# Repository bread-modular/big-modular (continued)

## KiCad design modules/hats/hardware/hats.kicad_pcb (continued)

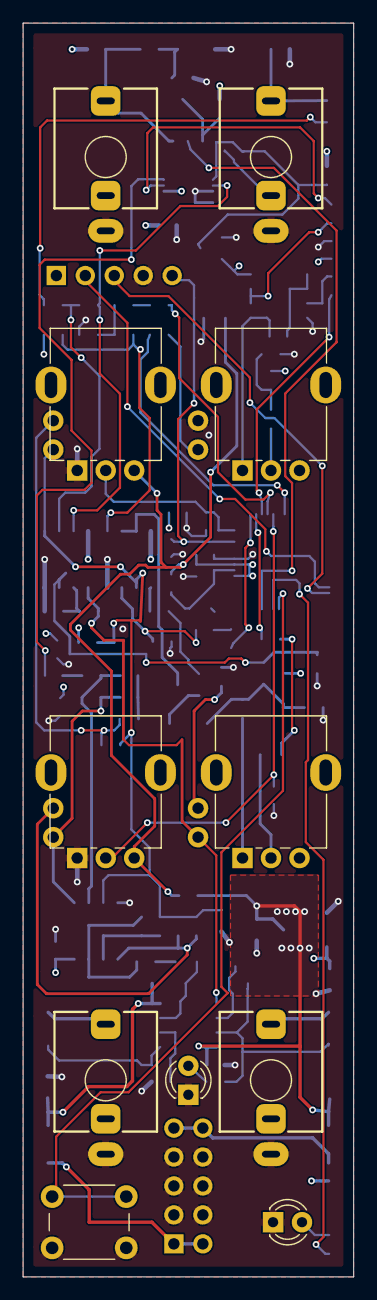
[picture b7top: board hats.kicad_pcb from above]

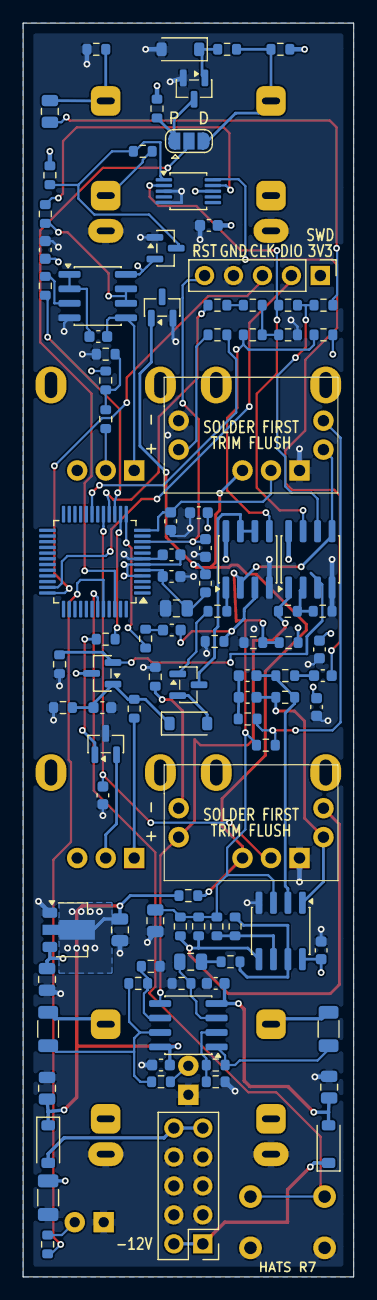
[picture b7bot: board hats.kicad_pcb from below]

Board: 4 copper layers, 29.0 x 110.0 mm, 113 parts (102 on the bottom side), 75 nets.

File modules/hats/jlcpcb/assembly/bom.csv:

Comment,Designator,Footprint,LCSC Part #,Quantity,Manufacturer,MPN
10u,"C1, C2, C4",C_0805_2012Metric,C15850,3,Samsung,CL21A106KAYNNNE
1u,"C3, C10, C21, C24",C_0805_2012Metric,C28323,4,Samsung,CL21B105KBFNNNE
100u,C5,C_1206_3216Metric,C15008,1,Samsung,CL31A107MQHNNNE
100n,"C6, C9, C11, C16, C19, C20, C22, C23, C25, C26",C_0603_1608Metric,C14663,10,YAGEO,CC0603KRX7R9BB104
4.7u,"C7, C18",C_0603_1608Metric,C19666,2,Samsung,CL10A475KO8NNNC
100p,"C8, C12",C_0603_1608Metric,C14858,2,Samsung,CL10C101JB8NNNC
1n,"C13, C14",C_0603_1608Metric,C1588,2,Samsung,CL10B102KB8NNNC
47u,C15,C_0805_2012Metric,C16780,1,Samsung,CL21A476MQYNNNE
10n,"C17, C27, C28",C_0603_1608Metric,C57112,3,FH (Guangdong Fenghua),0603B103K500NT
B5819W,"D1, D2, D4",D_SOD-123,C8598,3,CJ (Jiangsu Changjing),B5819W SL
1N4148W,D3,D_SOD-123,C81598,1,ST(Semtech),1N4148W
BAV199,D7,SOT-23,C40919,1,Nexperia,"BAV199,215"
600R@100MHz,FB1,L_0603_1608Metric,C1002,1,Sunlord,GZ1608D601TF
MMBT3904,Q1,SOT-23,C20526,1,CJ (Jiangsu Changjing),MMBT3904(RANGE:100-300)
SS8050,"Q2, Q4",SOT-23,C431710,2,MDD(Microdiode Semiconductor),SS8050
SS8550,Q3,SOT-23,C364314,1,MDD(Microdiode Semiconductor),SS8550
100k,"R1, R11, R12, R15, R27, R30, R31, R38, R39, R40, R45",R_0603_1608Metric,C25803,11,UNI-ROYAL,0603WAF1003T5E
10k,"R2, R21, R26, R29, R37, R42",R_0603_1608Metric,C25804,6,UNI-ROYAL,0603WAF1002T5E
22k,"R3, R20, R34, R49",R_0603_1608Metric,C31850,4,UNI-ROYAL,0603WAF2202T5E
1k,"R6, R8, R9, R10, R17, R22, R24, R25, R47, R48",R_0603_1608Metric,C21190,10,UNI-ROYAL,0603WAF1001T5E
330,"R7, R18, R19, R23, R28, R35, R51",R_0603_1608Metric,C23138,7,UNI-ROYAL,0603WAF3300T5E
33k,R13,R_0603_1608Metric,C4216,1,UNI-ROYAL,0603WAF3302T5E
470k,R14,R_0603_1608Metric,C23178,1,UNI-ROYAL,0603WAF4703T5E
200k,"R16, R36",R_0603_1608Metric,C25811,2,UNI-ROYAL,0603WAF2003T5E
1M,"R32, R33",R_0603_1608Metric,C22935,2,UNI-ROYAL,0603WAF1004T5E
20k,R41,R_0603_1608Metric,C4184,1,UNI-ROYAL,0603WAF2002T5E
1k,"R43, R46",R_1206_3216Metric,C2074262,2,ROHM,ESR18EZPF1001
51k,"R44, R50",R_0603_1608Metric,C23196,2,UNI-ROYAL,0603WAF5102T5E
HT7533-1,U1,SOT-89-3,C14289,1,Holtek,HT7533-1
STM32G071C8T6,U2,LQFP-48_7x7mm_P0.5mm,C529341,1,STMicroelectronics,STM32G071C8T6
MCP6002,"U4, U6, U8, U9",SOIC-8_3.9x4.9mm_P1.27mm,C7377,4,Microchip,MCP6002T-I/SN
TS5A23157,U5,TSSOP-10_3x3mm_P0.5mm,C11133,1,Texas Instruments,TS5A23157DGSR
TL072,U10,SOIC-8_3.9x4.9mm_P1.27mm,C6961,1,STMicroelectronics,TL072CDT

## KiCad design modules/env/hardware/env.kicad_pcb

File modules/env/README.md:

# ENV: MIDI envelope (6HP)

The ACID envelope on its own module: Bread Modular **ENV** on one ATtiny1616 at 5 V (the same HT7550-1 supply as our 8bit),
triggered by MIDI notes, with three envelope models, knob recording and a protected 0..5 V
output.

| Panel (top to bottom) | Circuit |
|---|---|
| **GATE IN**, **MIDI IN** (top row) | GATE: NPN buffer (~1.9 V threshold, ±12 V safe) + jack detect: a patched GATE IN bypasses MIDI notes. MIDI: 8bit / ACID NPN front end, JP1 protected/direct jumper |
| **ATTACK**, **RELEASE** | BM ENV time knobs, 50k dividers (attack = hold in HR mode), 30 mm apart |
| **MODE** button + **HR / AR / ASR** LEDs (one row) | Envelope model select (BM ENV algorithms); the selected LED stays lit |
| **REC** button + LED | Records the knob positions (4-bar loop on MIDI clock) |
| **ENV OUT**, **ENV** LED, **MIDI OUT** (bottom row) | Scaled DAC ~0..3.3 V (INT43V, codes 0..194) -> TL072 x1.51 -> 0..5 V, 1k 0.5 W series; the LED shows the envelope level (driven by the output amp). MIDI OUT is a passive thru wired to MIDI IN (daisy chain) |

**Status: S5 schematic (ERC 0, every net wired; adds R20 470k from ENV OUT to -12 V so a silent envelope idles at about -25 mV) + P7 THT placement + R2 manual routing (R1 + R20) (2 layers,
DRC 0, unconnected 0, parity 0; B silk JP1 / UPDI labels); 6HP panel. JLCPCB export in
[`jlcpcb/`](jlcpcb/README.md) (S5/R2, 2026-11-18, bottom Economic, 37 parts / 19 rows), not supplier-accepted, not built.
Firmware in [`firmware/`](firmware/README.md) (JP1 p/d builds), compiled, not bench-tested.** R5-R8 (HR/AR/ASR/REC indicators) are now 1k; R13 (ENV LED) was already 1k.

**Firmware contract:** 4.34 V DAC setting at a 5 V supply, scale the envelope to DAC codes
0..194; use VDD for the knob ADC reference. Use JP1 **P/protected** for 3.3 V MIDI senders
(direct mode is 5 V logic only) and a 5 V-compatible UPDI programmer.

```sh
python3 -B tools/import_footprints.py   # one-time library import (pcbnew)
python3 -B tools/build_schematic.py     # schematic (placement by hand, wires by its router)
python3 -B tools/build_layout.py        # P7: THT placement + parked SMD. Do NOT rerun: the board is routed
(cd ../.. && python3 -B opt/kicad-tools/kicad_tools.py check --config modules/env/tools/kicad-project.json \
   --reports modules/env/research/check-NEW)
```

Read [`Code.md`](Code.md) before changing hardware.

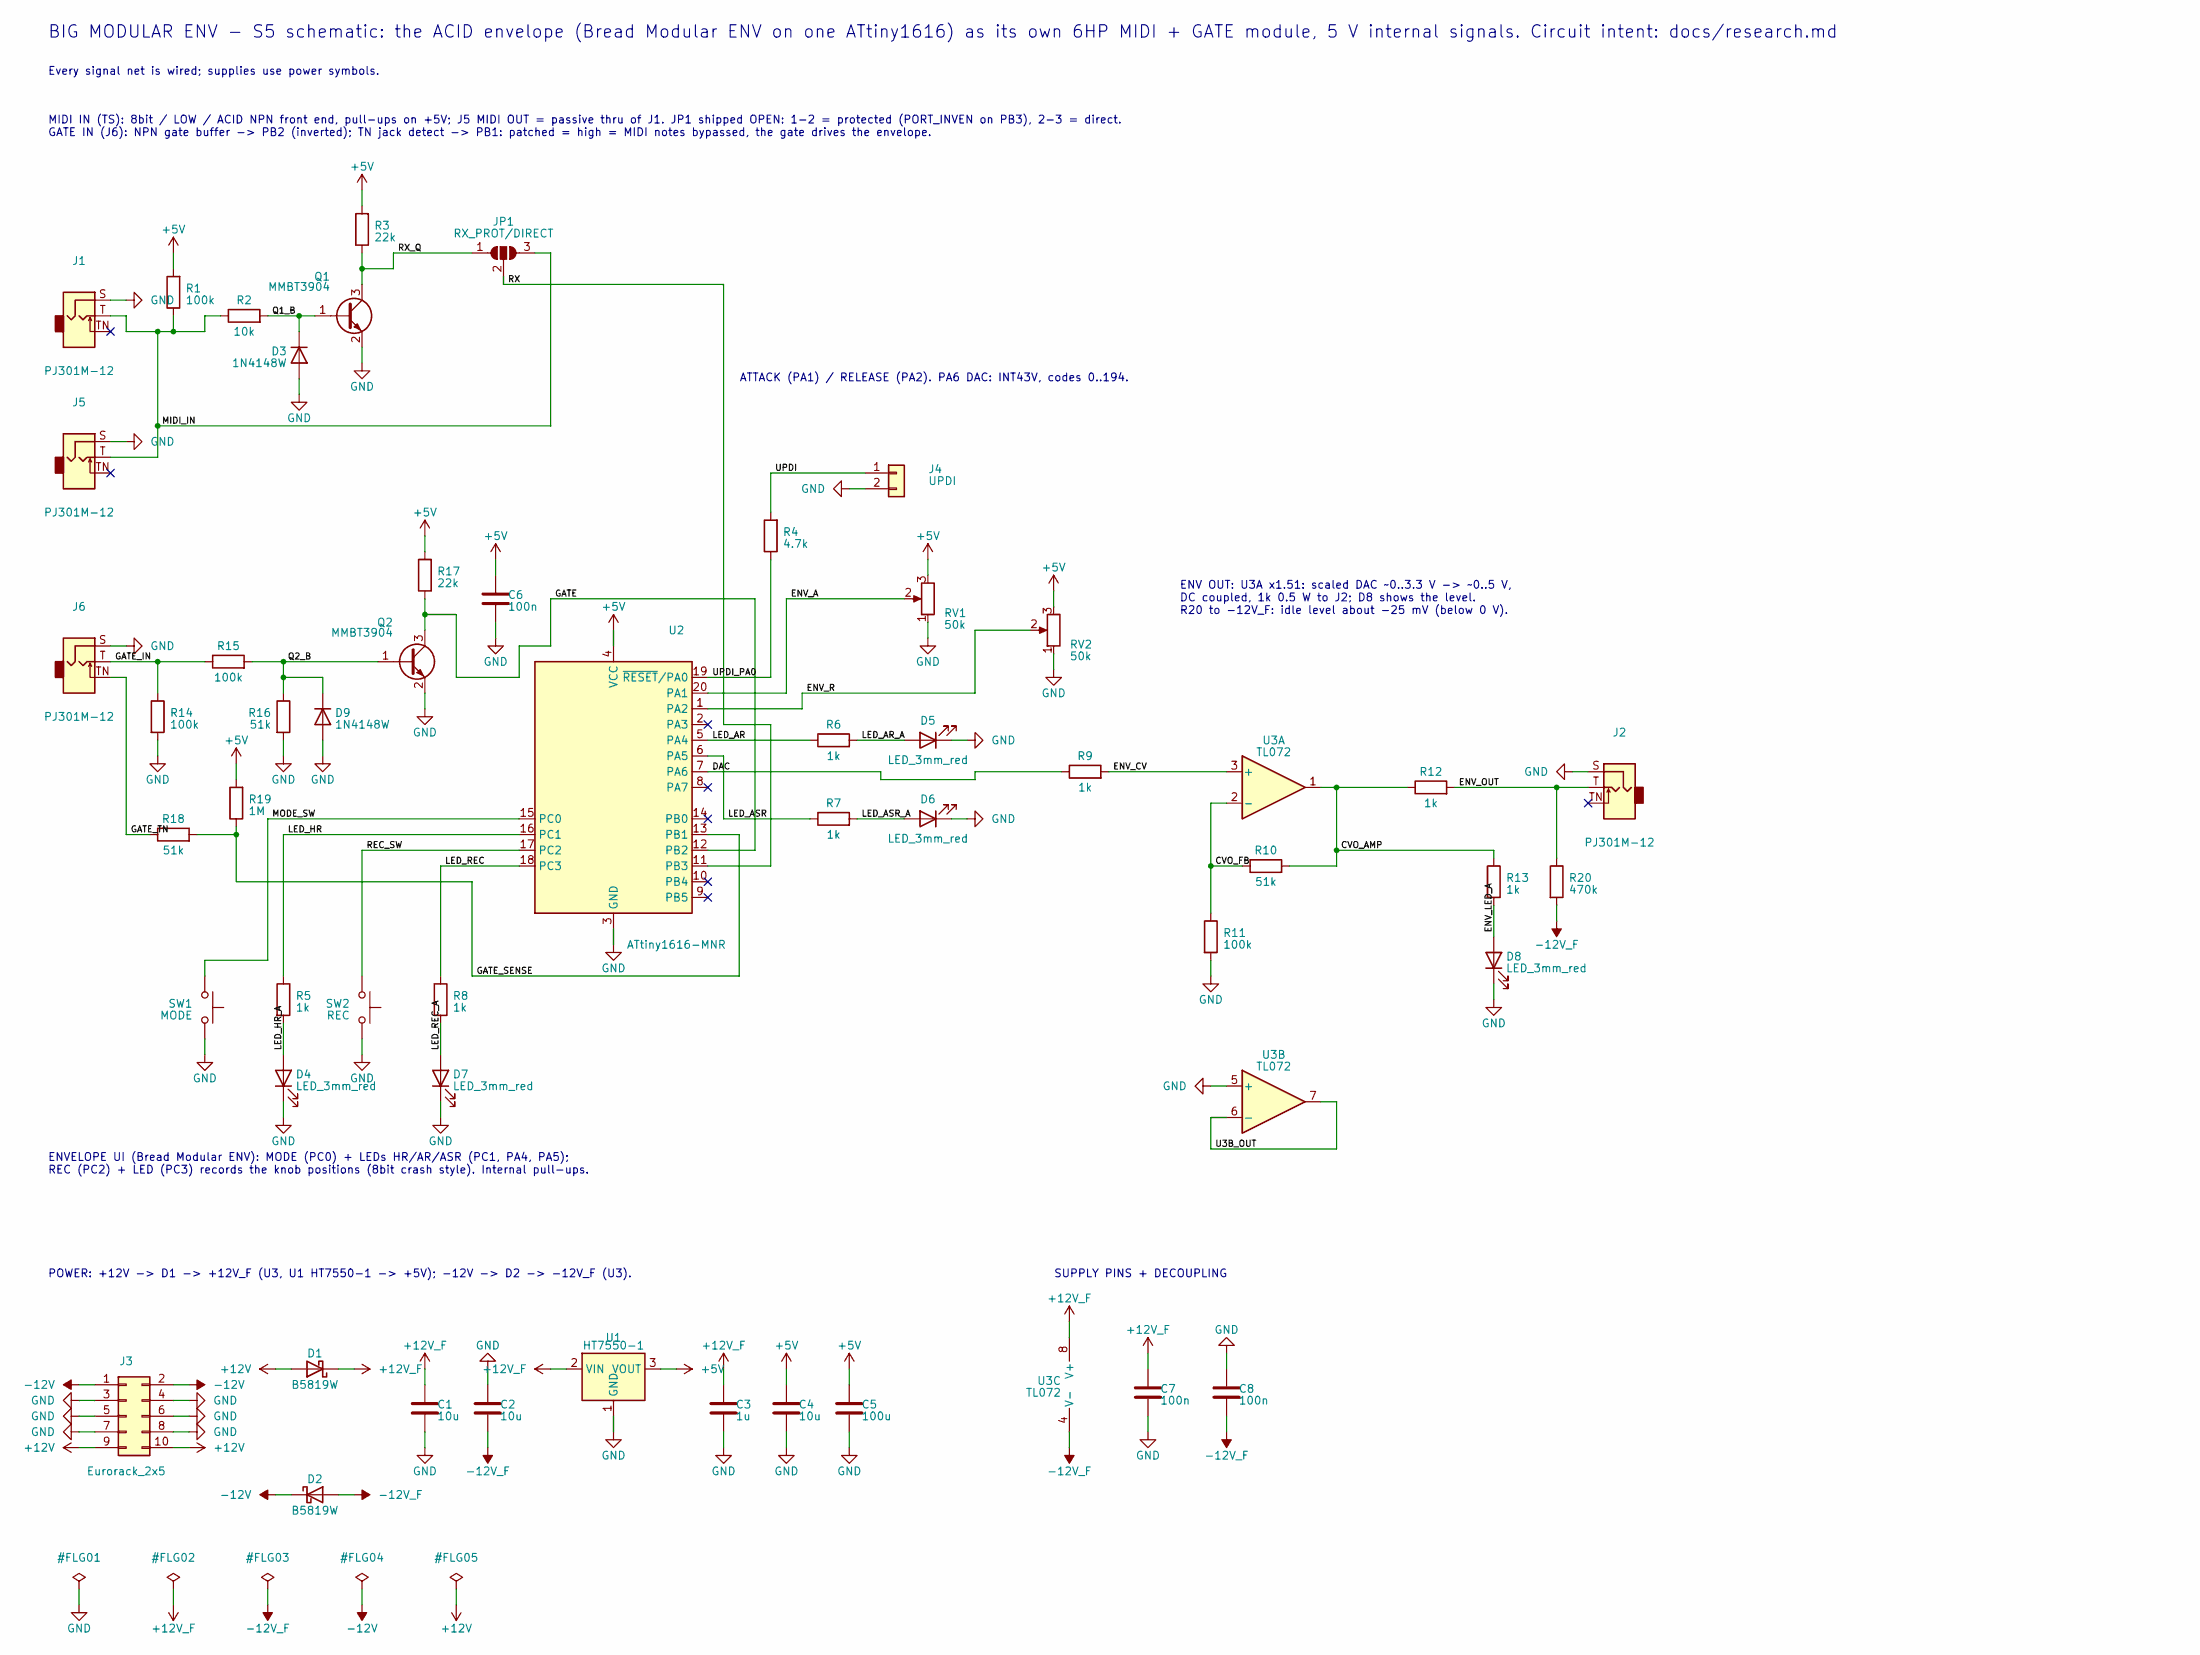
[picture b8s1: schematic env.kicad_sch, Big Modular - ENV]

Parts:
C1, C2, C4: 10u; C_0805_2012Metric; Voltage 25V; MPN CL21A106KAYNNNE; LCSC C15850
C3: 1u; C_0805_2012Metric; Voltage 50V; MPN CL21B105KBFNNNE; LCSC C28323
C5: 100u; C_1206_3216Metric; Voltage 6.3V; MPN CL31A107MQHNNNE; LCSC C15008
C6, C7, C8: 100n; C_0603_1608Metric; Voltage 50V; MPN CC0603KRX7R9BB104; LCSC C14663
D1, D2: B5819W; D_SOD-123; MPN B5819W SL; LCSC C8598
D3, D9: 1N4148W; D_SOD-123; MPN 1N4148W; LCSC C81598
D4, D5, D6, D7, D8: LED_3mm_red; LED_D3.0mm
J1, J2, J5, J6: PJ301M-12; Jack_3.5mm_QingPu_WQP-PJ301M-12_Vertical
J3: Eurorack_2x5; PinHeader_2x05_P2.54mm_Vertical
J4: UPDI; PinHeader_1x02_P2.54mm_Vertical
JP1: RX_PROT/DIRECT; SolderJumper-3_P1.3mm_Open_RoundedPad1.0x1.5mm
Q1, Q2: MMBT3904; SOT-23; MPN MMBT3904(RANGE:100-300); LCSC C20526
R1, R11, R14, R15: 100k; R_0603_1608Metric; MPN 0603WAF1003T5E; LCSC C25803
R2: 10k; R_0603_1608Metric; MPN 0603WAF1002T5E; LCSC C25804
R3, R17: 22k; R_0603_1608Metric; MPN 0603WAF2202T5E; LCSC C31850
R4: 4.7k; R_0603_1608Metric; MPN 0603WAF4701T5E; LCSC C23162
R5, R6, R7, R8, R9, R13: 1k; R_0603_1608Metric; MPN 0603WAF1001T5E; LCSC C21190
R10, R16, R18: 51k; R_0603_1608Metric; MPN 0603WAF5102T5E; LCSC C23196
R12: 1k; R_1206_3216Metric; MPN ESR18EZPF1001; LCSC C2074262
R19: 1M; R_0603_1608Metric; MPN 0603WAF1004T5E; LCSC C22935
R20: 470k; R_0603_1608Metric; MPN 0603WAF4703T5E; LCSC C23178
RV1, RV2: 50k; Potentiometer_RV09
SW1: MODE; SW_PUSH_6mm_H7.3mm; MPN 6x6x7 mm THT tact switch, 4 pins (gener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
SW2: REC; SW_PUSH_6mm_H7.3mm; MPN 6x6x7 mm THT tact switch, 4 pins (gener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
U1: HT7550-1; SOT-89-3; MPN HT7550-1; LCSC C16106
U2: ATtiny1616-MNR; VQFN-20-1EP_3x3mm_P0.4mm_EP1.7x1.7mm; MPN ATTINY1616-MNR; LCSC C507118
U3: TL072; SOIC-8_3.9x4.9mm_P1.27mm; MPN TL072CDT; LCSC C6961

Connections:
+5V: C4.1, C5.1, C6.1, R1.2, R3.2, R17.2, R19.2, RV1.3, RV2.3, U1.3 (VOUT), U2.4 (VCC)
+12V: D1.2 (A), J3.9, J3.10
+12V_F: C1.1, C3.1, C7.1, D1.1 (K), U1.2 (VIN), U3.8 (V+)
-12V: D2.1 (K), J3.1, J3.2
-12V_F: C2.2, C8.2, D2.2 (A), R20.2, U3.4 (V-)
/CVO_AMP: R10.2, R12.1, R13.1, U3.1
/CVO_FB: R10.1, R11.1, U3.2 (-)
/DAC: R9.1, U2.7 (PA6)
/ENV_A: RV1.2, U2.20 (PA1)
/ENV_CV: R9.2, U3.3 (+)
/ENV_LED_A: D8.2 (A), R13.2
/ENV_OUT: J2.T, R12.2, R20.1
/ENV_R: RV2.2, U2.1 (PA2)
/GATE: Q2.3 (C), R17.1, U2.12 (PB2)
/GATE_IN: J6.T, R14.1, R15.1
/GATE_SENSE: R18.2, R19.1, U2.13 (PB1)
/GATE_TN: J6.TN, R18.1
/LED_AR: R6.1, U2.5 (PA4)
/LED_AR_A: D5.2 (A), R6.2
/LED_ASR: R7.1, U2.6 (PA5)
/LED_ASR_A: D6.2 (A), R7.2
/LED_HR: R5.1, U2.16 (PC1)
/LED_HR_A: D4.2 (A), R5.2
/LED_REC: R8.1, U2.18 (PC3)
/LED_REC_A: D7.2 (A), R8.2
/MIDI_IN: J1.T, J5.T, JP1.3 (B), R1.1, R2.1
/MODE_SW: SW1.1, U2.15 (PC0)
/Q1_B: D3.1 (K), Q1.1 (B), R2.2
/Q2_B: D9.1 (K), Q2.1 (B), R15.2, R16.1
/REC_SW: SW2.1, U2.17 (PC2)
/RX: JP1.2 (C), U2.11 (PB3)
/RX_Q: JP1.1 (A), Q1.3 (C), R3.1
/U3B_OUT: U3.6 (-), U3.7
/UPDI: J4.1, R4.2
/UPDI_PA0: R4.1, U2.19 (~RESET/PA0)
GND: C1.2, C2.1, C3.2, C4.2, C5.2, C6.2, C7.2, C8.1, D3.2 (A), D4.1 (K), D5.1 (K), D6.1 (K), D7.1 (K), D8.1 (K), D9.2 (A), J1.S, J2.S, J3.3, J3.4, J3.5, J3.6, J3.7, J3.8, J4.2, J5.S, J6.S, Q1.2 (E), Q2.2 (E), R11.2, R14.2, R16.2, RV1.1, RV2.1, SW1.2, SW2.2, U1.1 (GND), U2.3 (GND), U2.21 (GND), U3.5 (+)

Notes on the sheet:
ATTACK (PA1) / RELEASE (PA2). PA6 DAC: INT43V, codes 0..194.
Every signal net is wired; supplies use power symbols.
ENV OUT: U3A x1.51: scaled DAC ~0..3.3 V -> ~0..5 V, DC coupled, 1k 0.5 W to J2; D8 shows the level. R20 to -12V_F: idle level about -25 mV (below 0 V).
ENVELOPE UI (Bread Modular ENV): MODE (PC0) + LEDs HR/AR/ASR (PC1, PA4, PA5); REC (PC2) + LED (PC3) records the knob positions (8bit crash style). Internal pull-ups.
MIDI IN (TS): 8bit / LOW / ACID NPN front end, pull-ups on +5V; J5 MIDI OUT = passive thru of J1. JP1 shipped OPEN: 1-2 = protected (PORT_INVEN on PB3), 2-3 = direct. GATE IN (J6): NPN gate buffer -> PB2 (inverted); TN jack detect -> PB1: patched = high = MIDI notes bypassed, the gate drives the en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
BIG MODULAR ENV - S5 schematic: the ACID envelope (Bread Modular ENV on one ATtiny1616) as its own 6HP MIDI + GATE module, 5 V internal signals. Circuit intent: docs/research.md
SUPPLY PINS + DECOUPLING
POWER: +12V -> D1 -> +12V_F (U3, U1 HT7550-1 -> +5V); -12V -> D2 -> -12V_F (U3).

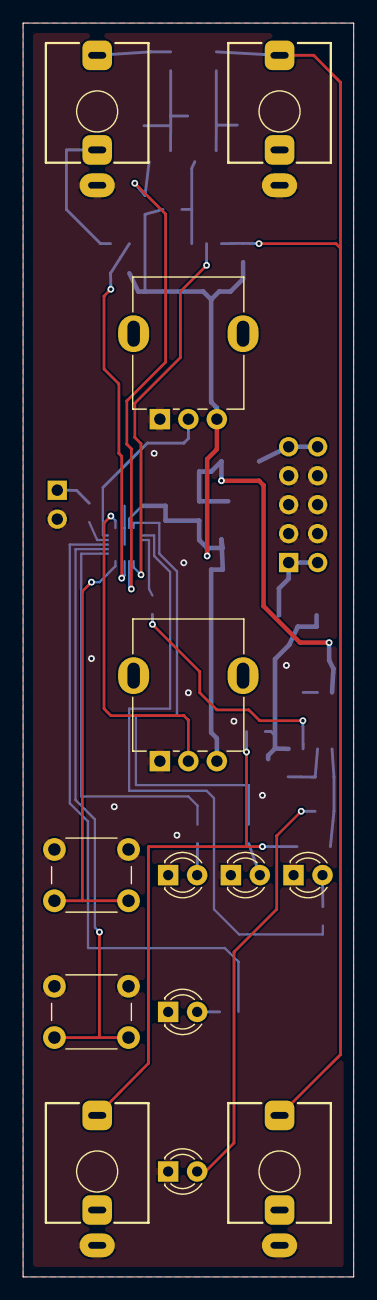
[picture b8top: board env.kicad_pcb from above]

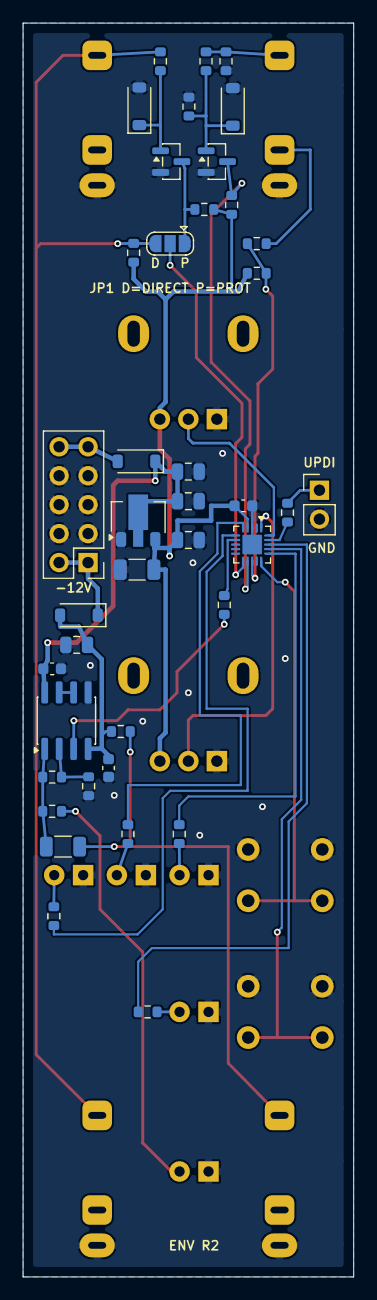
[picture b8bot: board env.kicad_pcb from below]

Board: 2 copper layers, 29.0 x 110.0 mm, 53 parts (40 on the bottom side), 36 nets.

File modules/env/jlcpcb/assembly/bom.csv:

Comment,Designator,Footprint,LCSC Part #,Quantity,Manufacturer,MPN
10u,"C1, C2, C4",C_0805_2012Metric,C15850,3,Samsung,CL21A106KAYNNNE
1u,C3,C_0805_2012Metric,C28323,1,Samsung,CL21B105KBFNNNE
100u,C5,C_1206_3216Metric,C15008,1,Samsung,CL31A107MQHNNNE
100n,"C6, C7, C8",C_0603_1608Metric,C14663,3,YAGEO,CC0603KRX7R9BB104
B5819W,"D1, D2",D_SOD-123,C8598,2,CJ (Jiangsu Changjing),B5819W SL
1N4148W,"D3, D9",D_SOD-123,C81598,2,ST(Semtech),1N4148W
MMBT3904,"Q1, Q2",SOT-23,C20526,2,CJ (Jiangsu Changjing),MMBT3904(RANGE:100-300)
100k,"R1, R11, R14, R15",R_0603_1608Metric,C25803,4,UNI-ROYAL,0603WAF1003T5E
10k,R2,R_0603_1608Metric,C25804,1,UNI-ROYAL,0603WAF1002T5E
22k,"R3, R17",R_0603_1608Metric,C31850,2,UNI-ROYAL,0603WAF2202T5E
4.7k,R4,R_0603_1608Metric,C23162,1,UNI-ROYAL,0603WAF4701T5E
1k,"R5, R6, R7, R8, R9, R13",R_0603_1608Metric,C21190,6,UNI-ROYAL,0603WAF1001T5E
51k,"R10, R16, R18",R_0603_1608Metric,C23196,3,UNI-ROYAL,0603WAF5102T5E
1k,R12,R_1206_3216Metric,C2074262,1,ROHM,ESR18EZPF1001
1M,R19,R_0603_1608Metric,C22935,1,UNI-ROYAL,0603WAF1004T5E
470k,R20,R_0603_1608Metric,C23178,1,UNI-ROYAL,0603WAF4703T5E
HT7550-1,U1,SOT-89-3,C16106,1,Holtek,HT7550-1
ATtiny1616-MNR,U2,VQFN-20-1EP_3x3mm_P0.4mm_EP1.7x1.7mm,C507118,1,Microchip,ATTINY1616-MNR
TL072,U3,SOIC-8_3.9x4.9mm_P1.27mm,C6961,1,STMicroelectronics,TL072CDT

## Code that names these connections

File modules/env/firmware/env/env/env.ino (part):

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// GATE IN:
//
//   * Gate: MIDI note on/off (channel 1), or GATE IN when a cable is patched
//     (PB1 jack detect high): then MIDI notes are bypassed and the jack gate
//     (PB2, inverted by Q2) drives the envelope.
//   * Envelope (BM ENV 1.2.1) on the DAC (PA6 -> TL072 x1.51 -> ENV OUT
//     0..5 V). ATTACK (PA1, hold in HR) and RELEASE (PA2) set the times, plus
//     MIDI CC22 / CC75 as BM. MODE (PC0, a click) cycles HR / AR / ASR, stored
//     in EEPROM; the selected model's LED (PC1 / PA4 / PA5) stays lit at
//     10 % (the ENV LED at the jack shows the envelope level).
//   * REC (PC2 / LED PC3): 4-bar ATTACK/RELEASE motion recorder on MIDI clock
//     (shared lib/CvRecorder, as ACID): click to record (LED blinks), after
//     4 bars it loops (LED solid), hold REC + turn a knob to overdub it,
//     click again for the live knobs.
//
// The USART runs receive-only: its TX pin PB2 is GATE IN on this board.
// ----------------------------------------------------------------------------

// JP1 on the ENV carrier picks the MIDI input path (set by ../../jumper.sh):
//   P (protected) = NPN front end (Q1), which inverts the UART data -> 1
//   D (direct)    = jack tip straight to PB3, 5 V logic senders only -> 0
#ifndef MIDI_RX_INVERT
#error "MIDI_RX_INVERT must be set: build with ../../compile.sh p|d"
#endif

#define PIN_CV1          PIN_PA1   // ATTACK knob (hold time in HR)
#define PIN_CV2          PIN_PA2   // RELEASE knob
#define MODE_BUTTON_PIN  PIN_PC0   // envelope model (BM ENV algo button)
#define LED_HR           PIN_PC1
#define LED_AR           PIN_PA4
#define LED_ASR          PIN_PA5
#define REC_BUTTON_PIN   PIN_PC2
#define REC_LED_PIN      PIN_PC3
#define GATE_IN_PIN      PIN_PB2   // Q2 collector: LOW = gate high at the jack
#define GATE_SENSE_PIN   PIN_PB1   // HIGH = GATE IN patched (TN open)

#define ALGO_HOLD_RELEASE 0
#define ALGO_ATTACK_RELEASE 1
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#define GATE_SENSE_MS 20           // jack detect must hold this long to switch

// MODE LED brightness: TCA0 in split mode (TCD0 is millis), 20 MHz / 256 /
// 256 = 305 Hz, duty = count / 256. PA4 (WO4, HCMP1) and PA5 (WO5, HCMP2)
// are hardware PWM. PC1 has no TCA output, so the low counter switches it in
// software (LCMP0 on, LUNF off); those two interrupts run only while the HR
// LED is lit.
#define LED_PERCENT 10             // brightness of the selected MODE LED
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EnvelopeGenerator *envelope;

ToggleMode algoMode(MODE_BUTTON_PIN, 1, 3);        // EEPROM index 1, as BM
CvRecorder recorder(REC_BUTTON_PIN, REC_LED_PIN);

const uint8_t modeLeds[3] = {LED_HR, LED_AR, LED_ASR};

uint16_t liveCV1 = 0;              // ATTACK / RELEASE knobs (recorder input)
uint16_t liveCV2 = 0;
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int modCV2 = 0;                    // MIDI CC75 (release time)

bool midiGate = false;
byte gateNote = 0;                 // note that holds the gate
bool gatePatched = false;          // debounced PB1 jack detect
byte selectedLed = 0;              // index into modeLeds

void handleAlgoModeChange(byte newMode) {
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  TCA0.SPLIT.CTRLA = TCA_SPLIT_CLKSEL_DIV256_gc | TCA_SPLIT_ENABLE_bm;
}

// PC1 (HR) software PWM: the down-counting low counter matches LCMP0 =
// duty - 1, so PC1 is high for duty counts until the underflow.
ISR(TCA0_LCMP0_vect) {
  PORTC.OUTSET = PIN1_bm;
  TCA0.SPLIT.INTFLAGS = TCA_SPLIT_LCMP0_bm;
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
  uint8_t outputs = 0;
  if (duty && led == 1) {
    outputs = TCA_SPLIT_HCMP1EN_bm;    // PA4 (AR)
  } else if (duty && led == 2) {
    outputs = TCA_SPLIT_HCMP2EN_bm;    // PA5 (ASR)
  }
  TCA0.SPLIT.CTRLB = outputs;

  const bool soft = duty && led == 0;  // PC1 (HR)
  TCA0.SPLIT.INTCTRL = soft ? TCA_SPLIT_LUNF_bm | TCA_SPLIT_LCMP0_bm : 0;
  if (!soft) {
    PORTC.OUTCLR = PIN1_bm;
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}

void handleNoteOff(byte channel, byte note, byte velocity) {
  // Only the latest note closes the gate: an overlapping (legato) note keeps
  // the envelope open instead of releasing it under the held note.
  if (note == gateNote) {
    midiGate = false;
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  liveCV2 = analogRead(PIN_CV2);
}

// PB1 jack detect, debounced: the TN contact opens / closes while a plug
// slides in, so the new state must hold GATE_SENSE_MS before it switches.
void updateGateSense() {
  static bool lastRaw = false;
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// Envelope gate: GATE IN when patched (MIDI notes bypassed), else MIDI.
bool currentGate() {
  if (gatePatched) {
    return !(VPORTB.IN & PIN2_bm);     // Q2 inverts: PB2 low = gate high
  }
  return midiGate;
}
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
void setup() {
  // Unused pins (no-connect on the carrier): pulled up, not floating.
  pinMode(PIN_PA3, INPUT_PULLUP);
  pinMode(PIN_PA7, INPUT_PULLUP);
  pinMode(PIN_PB0, INPUT_PULLUP);
  pinMode(PIN_PB4, INPUT_PULLUP);
  pinMode(PIN_PB5, INPUT_PULLUP);

  // GATE IN: R17 22k pull-up and R19 1M jack-detect pull-up on the board.
  pinMode(GATE_IN_PIN, INPUT);
  pinMode(GATE_SENSE_PIN, INPUT);
  gatePatched = VPORTB.IN & PIN1_bm;

  // MIDI, receive only (serialMIDI.h): listen to channel 1 only.
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  MIDI.turnThruOff();
#if MIDI_RX_INVERT
  // JP1 = P: the NPN input stage inverts the MIDI UART data, so invert
  // PB3 (RX) in the port before the USART samples it.
  PORTB.PIN3CTRL |= PORT_INVEN_bm;
#endif
  MIDI.setHandleNoteOn(handleNoteOn);
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  (void)analogRead(PIN_CV1);       // throwaway warm-up read
  readKnobs();

  // DAC0 on PA6 with the internal 4.34 V reference (needs VDD >= 4.75 V,
  // research.md 6); EnvelopeGenerator scales the envelope to 0..194.
  VREF.CTRLA = (VREF.CTRLA & ~VREF_DAC0REFSEL_gm) | VREF_DAC0REFSEL_4V34_gc;
  VREF.CTRLB |= VREF_DAC0REFEN_bm;
  DAC0.DATA = 0;
  EnvelopeGenerator::envDacPin(false);  // idle: PA6 held at 0 V

  // Envelope model selector (MODE + three LEDs)
  for (byte i = 0; i < 3; i++) {
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
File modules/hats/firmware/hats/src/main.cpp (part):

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// HATS S4 firmware (STM32G071C8T6 U2): Bread Modular NOISE + HIHAT on one
// MCU, plus the PWM CUTOFF vactrol and the shared 4-bar REC recorder.
//
//   PA4 DAC1_OUT1  white noise (BM NOISE, -> R6 / U4A, blue high-pass)
//   PA5 DAC1_OUT2  velocity (BM HIHAT)
//   PA2 / PA3      gate / open hat (BM HIHAT: notes > 60 open)
//   PA1 ADC_IN1    NOISE TONE knob (RV1)
//   PA6 ADC_IN6    CUTOFF knob (RV3)
//   PB0 TIM3_CH3   CUTOFF vactrol LED PWM (R51 -> U11), 31.25 kHz, dithered
//   PB4 / PB5      REC button (pull-up) / REC LED (R48 -> D6)
//   PB7 USART1_RX  MIDI 31250 baud, all channels; RXINV for JP1 = P
//
//   REC (shared CvRecorder, hold REC while looping = overdub): lane 1
//   CUTOFF, lane 2 NOISE TONE, 4 bars on
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
// JP1 on the HATS carrier picks the MIDI input path (set by ../jumper.sh):
//   P (protected) = NPN front end (Q1), which inverts the UART data -> 1
//   D (direct)    = jack tip straight to PB7, as Bread Modular     -> 0
#ifndef MIDI_RX_INVERT
#error "MIDI_RX_INVERT must be set: build with ../compile.sh p|d"
#endif

#define GATE_PIN       PIN_PA(2)
#define OPEN_HAT_PIN   PIN_PA(3)
#define REC_BUTTON_PIN PIN_PB(4)
#define REC_LED_PIN    PIN_PB(5)

#define ADC_CH_TONE    1   // PA1
#define ADC_CH_CUTOFF  6   // PA6

#define ADC_CHANNELS 2
#define ADC_SCANS 16   // averaged per reading, as the 16x oversampling before
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static hats::PwmDither dither;
static hats::MidiParser midi;
static hats::HihatOut hihat;
static CvRecorder recorder(REC_BUTTON_PIN, REC_LED_PIN);

static uint8_t cc74 = 0;
static uint16_t liveCutoff = 0;   // knobs, 0..1023 (recorder input)
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
static void gpioInit() {
    RCC->IOPENR |= RCC_IOPENR_GPIOAEN | RCC_IOPENR_GPIOBEN;
    pinMode(GATE_PIN, OUTPUT);
    pinMode(OPEN_HAT_PIN, OUTPUT);
    digitalWrite(GATE_PIN, LOW);
    digitalWrite(OPEN_HAT_PIN, LOW);
    setMode(GPIOA, 1, 3);   // NOISE TONE, analog
    setMode(GPIOA, 6, 3);   // CUTOFF, analog
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    while (n--) {}
}

// Arms the stopped ADC: every TIM6 update then converts PA1 and PA6 once
// (2 x 3.25 us of the 10 us tick) into adcBuf, from its start.
static void adcStart() {
    DMA1_Channel1->CCR = 0;
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
// The mean of the last ADC_SCANS scans, 12 -> 10 bit as BM analogRead. An
// overrun stops the DMA requests and would shift the channel order in the
// ring: restart the scan from PA1.
static void readKnobs() {
    if (ADC1->ISR & ADC_ISR_OVR) {
        adcStop();
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            default:
                continue;
        }
        digitalWrite(GATE_PIN, hihat.gate ? HIGH : LOW);
        digitalWrite(OPEN_HAT_PIN, hihat.open ? HIGH : LOW);
        DAC1->DHR12R2 = hats::dac12(hihat.velocity);
    }
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
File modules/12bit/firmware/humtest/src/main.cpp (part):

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// which S3 takes off the MCU supply. Hum gone = it comes through the buffers'
// supply (VDD/VDDA), which S3 does not change.
//
//   PA4 / PA5      DAC1_OUT1 / OUT2, mid-scale, never changed
//   PA0 PA1 PA6 PA7  CV + P1..P3, the clapsnare ADC scan (values not used)
//   PB7 USART1_RX  MIDI, set up as the clapsnare `p` build, bytes dropped
//   PB4            MODE button (internal pull-up): next step
//   PB5            MODE LED (R7 -> D1)
//
// SysTick 1 ms runs in every step (button + LED). g_step holds the step and
// g_scanCount / g_sampleCount count the 1 kHz scans or reads and the sample
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
#include "stm32g0xx.h"

#define ADC_CH_CV 0   // PA0
#define ADC_CH_P1 1   // PA1
#define ADC_CH_P2 6   // PA6
#define ADC_CH_P3 7   // PA7

#define ADC_CHANNELS 4
#define ADC_SCANS 16   // averaged per reading (step 6)
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    }
}

// One ascending scan: PA0 (CV), PA1 (P1), PA6 (P2), PA7 (P3); values dropped.
static void scanKnobs() {
    ADC1->CR |= ADC_CR_ADSTART;
    for (int i = 0; i < 4; i++) {
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
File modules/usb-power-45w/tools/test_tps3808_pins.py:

"""TPS3808G01 pin-identity regression (S6 had SENSE=3 / MR=5; TI DBV is MR=3 / SENSE=5).

Run from the repository root (needs kicad-cli; reads, never writes, the module):
  python3 -B -m unittest discover -s modules/usb-power-45w/tools -p 'test_*.py' -v

The old map was self-consistent: symbol, circuit table and verifier table all agreed.
These tests rebuild that state (circuit() and CRIT reverted too) and require the
manufacturer-derived check in verify_design.py to reject it on its own.
"""
import copy
import shutil
import subprocess
import sys
import tempfile
import unittest
import xml.etree.ElementTree as ET
from pathlib import Path
from unittest import mock

sys.path.insert(0, str(Path(__file__).resolve().parent))
import circuit45  # noqa: E402
import verify_design  # noqa: E402
from sexp import parse, nodes, one, walk  # noqa: E402

MODULE = Path(__file__).resolve().parents[1]
HW = MODULE / 'hardware'
OLD_COMMIT = '077905c'          # last commit with the swapped TPS3808 map
OLD_PINS = {'U10': {'1': 'RESET_N', '2': 'GND', '3': 'POR_SENSE', '4': None, '5': 'RESET_BTN_N', '6': 'V3V3'},
            'U11': {'1': 'START_READY', '2': 'GND', '3': 'START_SENSE', '4': 'START_CT', '5': 'RESET_N', '6': 'V3V3'}}
OLD_CRIT = {'U10': {1: 'RESET_N', 2: 'GND', 3: 'POR_SENSE', 5: 'RESET_BTN_N', 6: 'V3V3'},
            'U11': {1: 'START_READY', 2: 'GND', 3: 'START_SENSE', 4: 'START_CT', 5: 'RESET_N', 6: 'V3V3'}}


def export_netlist(sch, out):
    subprocess.run(['kicad-cli', 'sch', 'export', 'netlist', '--format', 'kicadxml', '-o', str(out), str(sch)],
                   check=True, stdout=subprocess.DEVNULL)
    return out


def symbol_pins(lib_file, name='TPS3808G01'):
    sym = {s[1]: s for s in nodes(parse(Path(lib_file).read_text()), 'symbol')}[name]
    plain = lambda n: n[:-2] if n.endswith('_N') else n
    return {one(p, 'number')[1]: plain(one(p, 'name')[1]) for p in walk(sym, 'pin')}


def old_circuit(pre_s7=False):
    parts = copy.deepcopy(circuit45.circuit())
    for p in parts:
        if p['ref'] in OLD_PINS:
            p['pins'] = dict(OLD_PINS[p['ref']])
    if pre_s7:   # the committed pre-fix hardware still has the second parallel header J3 (removed in S7)
        for p in parts:                  # and the unnamed U4 RT net (S7 names it RT_U4)
            p['pins'] = {n: ('_RT_U4' if v == 'RT_U4' else v) for n, v in p['pins'].items()}
        j2 = next(p for p in parts if p['ref'] == 'J2')
        j2['fields']['Note'] = PRE_S7_HEADER_NOTE
        for k in PRE_S7_J2_DROPPED:                 # S7 R2 added the Wurth MPN/Manufacturer; 077905c had none
            assert j2['fields'].pop(k, None), k
        j3 = copy.deepcopy(j2)
        j3['ref'] = 'J3'
        parts.append(j3)
    return parts


PRE_S7_J2_DROPPED = ('MPN', 'Manufacturer')
PRE_S7_FP = {'IDC16': 'IDC-Header_2x08_P2.54mm_Vertical'}   # 077905c footprint; S7 R2 pins the Wurth 61201621621 land
PRE_S7_HEADER_NOTE = ('Hand-soldered shrouded 16-pin box header, pin 1 = -12V (red stripe). J2 and J3 are in '
                      'parallel: use both cables above ~1.5 A per rail. CV/GATE (13-16) open')


def mutate(src, dst, swap_symbol, swap_nets):
    """swap_symbol: libpart and pin functions use the old SENSE=3/MR=5 names.
    swap_nets: U10/U11 pins 3 and 5 exchange nets (the old circuit table)."""
    tree = ET.parse(src)
    root = tree.getroot()
    if swap_symbol:
        lib = next(p for p in root.iter('libpart') if p.get('part') == 'TPS3808G01')
        names = {x.get('num'): x for x in lib.findall('pins/pin')}
        names['3'].set('name', 'SENSE')
        names['5'].set('name', 'MR_N')
    for node in root.iter('node'):
        if node.get('ref') in OLD_PINS and node.get('pin') in ('3', '5'):
            pin = node.get('pin')
            other = '5' if pin == '3' else '3'
            func = node.get('pinfunction').removesuffix('_' + pin)
            if swap_nets:                       # same net now reaches the other physical pin
                node.set('pin', other)
                pin = other
                if not swap_symbol:             # fixed symbol: the pin keeps its datasheet name
                    func = {'SENSE': 'MR_N', 'MR_N': 'SENSE'}[func]
            elif swap_symbol:                   # old symbol names on unchanged nets
                func = {'SENSE': 'MR_N', 'MR_N': 'SENSE'}[func]
            node.set('pinfunction', f'{func}_{pin}')
    tree.write(dst)
    return dst


@unittest.skipUnless(shutil.which('kicad-cli'), 'kicad-cli required')
class TPS3808PinIdentity(unittest.TestCase):
    @classmethod
    def setUpClass(cls):
        cls.tmp = Path(tempfile.mkdtemp(prefix='tps3808-pins-'))
        cls.netlist = export_netlist(HW / 'usb-power-45w-system.kicad_sch', cls.tmp / 'current.xml')

    @classmethod
    def tearDownClass(cls):
        shutil.rmtree(cls.tmp)

    def verify(self, netlist, hardware=HW, root=None):
        return verify_design.verify(netlist, hardware, hierarchy_root=root)

    def old_tables(self, pre_s7=False):
        crit = {**verify_design.CRIT, **OLD_CRIT}
        fp = {**verify_design.FP, **PRE_S7_FP} if pre_s7 else verify_design.FP
        return mock.patch.multiple(verify_design, circuit=lambda: old_circuit(pre_s7), CRIT=crit, FP=fp)

    def test_symbols_match_ti_table(self):
        self.assertEqual(verify_design.TPS3808_DBV, {'1': 'RESET', '2': 'GND', '3': 'MR', '4': 'CT', '5': 'SENSE', '6': 'VDD'})
        for lib in (MODULE / 'tools/USBPOWER45-src.kicad_sym', HW / 'USBPOWER45.kicad_sym'):
            self.assertEqual(symbol_pins(lib), verify_design.TPS3808_DBV, lib)

    def test_current_design_passes(self):
        self.assertTrue(self.verify(self.netlist)['exact_field_pin_NC_pad_parity'])

    def test_old_self_consistent_map_rejected(self):
        bad = mutate(self.netlist, self.tmp / 'old-both.xml', swap_symbol=True, swap_nets=True)
        with self.old_tables():
            with mock.patch.object(verify_design, 'check_tps3808'):   # without it the old map passes
                self.verify(bad)
            with self.assertRaisesRegex(AssertionError, 'TPS3808G01 symbol pin identity'):
                self.verify(bad)

    def test_fixed_symbol_with_old_nets_rejected(self):
        bad = mutate(self.netlist, self.tmp / 'old-nets.xml', swap_symbol=False, swap_nets=True)
        with self.old_tables(), self.assertRaisesRegex(AssertionError, 'TPS3808 role not on'):
            self.verify(bad)

    def test_old_symbol_with_fixed_nets_rejected(self):
        bad = mutate(self.netlist, self.tmp / 'old-symbol.xml', swap_symbol=True, swap_nets=False)
        with self.assertRaisesRegex(AssertionError, 'TPS3808G01 symbol pin identity'):
            self.verify(bad)

    def test_committed_old_hardware_rejected(self):
        """The real pre-fix native schematic, with its own circuit/CRIT tables restored."""
        repo = MODULE.parents[1]
        rel = MODULE.relative_to(repo) / 'hardware'
        ls = subprocess.run(['git', '-C', str(repo), 'ls-tree', '-r', '--name-only', OLD_COMMIT, str(rel)],
                            capture_output=True, text=True)
        if ls.returncode or not ls.stdout.strip():
            self.skipTest(f'git history {OLD_COMMIT} unavailable')
        old_hw = self.tmp / 'old/hardware'
        for name in ls.stdout.split():
            dst = old_hw / Path(name).relative_to(rel)
            dst.parent.mkdir(parents=True, exist_ok=True)
            dst.write_bytes(subprocess.run(['git', '-C', str(repo), 'show', f'{OLD_COMMIT}:{name}'],
                                           check=True, capture_output=True).stdout)
        old_root = old_hw / 'usb-power-45w.kicad_sch'     # historical filename of the S6 root at that commit
        old = export_netlist(old_root, self.tmp / 'old.xml')
        with self.old_tables(pre_s7=True):
            with mock.patch.object(verify_design, 'check_tps3808'):
                self.verify(old, old_hw, old_root)
            with self.assertRaisesRegex(AssertionError, 'TPS3808G01 symbol pin identity'):
                self.verify(old, old_hw, old_root)


if __name__ == '__main__':
    unittest.main()
